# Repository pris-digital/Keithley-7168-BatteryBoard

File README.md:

# Keithley-7168-BatteryBoard
BatteryBoard to replace the proprietary battery cells used into the keithley 7168 nanovolt scanner card

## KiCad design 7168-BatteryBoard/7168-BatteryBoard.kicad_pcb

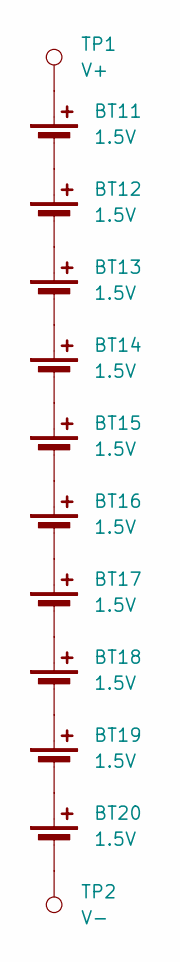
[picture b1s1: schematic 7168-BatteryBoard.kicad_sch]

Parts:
BT11, BT12, BT13, BT14, BT15, BT16, BT17, BT18, BT19, BT20: 1.5V; BatteryHolder_Keystone_2998_1x6.8mm
TP1: V+; Pin_D1.3mm_L11.0mm
TP2: V-; Pin_D1.3mm_L11.0mm

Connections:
unnamed: BT11.1 (+), TP1.1
unnamed: BT11.2 (-), BT12.1 (+)
unnamed: BT12.2 (-), BT13.1 (+)
unnamed: BT13.2 (-), BT14.1 (+)
unnamed: BT14.2 (-), BT15.1 (+)
unnamed: BT15.2 (-), BT16.1 (+)
unnamed: BT16.2 (-), BT17.1 (+)
unnamed: BT17.2 (-), BT18.1 (+)
unnamed: BT18.2 (-), BT19.1 (+)
unnamed: BT19.2 (-), BT20.1 (+)
unnamed: BT20.2 (-), TP2.1

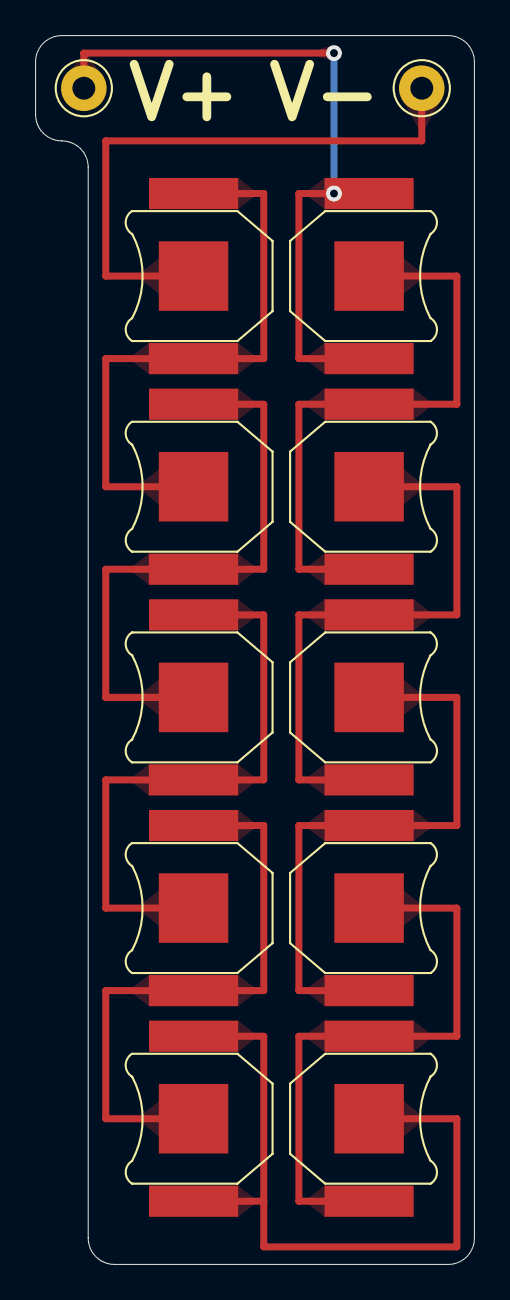
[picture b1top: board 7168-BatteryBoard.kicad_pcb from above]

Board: 2 copper layers, 25.0 x 70.0 mm, 12 parts (0 on the bottom side), 11 nets.
